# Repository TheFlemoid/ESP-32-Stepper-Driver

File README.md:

### ESP-WROOM-32 Based Stepper Motor Controller

PCB integrating an ESP-WROOM-32 microcontroller with two A4988/DRV8825 stepper motor drivers.

This is a four layer PCB that I originally designed this for an ESP-32 controlled, NEMA17 powered robot.  However it can also be useful for any other application requiring microcontroller control, stepper motors, and any form of SPI or I2C peripheral.

-----

Before connecting and driving the DRV8825, ensure that you set the current limit on both DRV8825/A4988 stepper drivers.

Features include:
 - 'Battery drive'.  Drive the board through a high voltage li-ion or LiPo battery, but enjoy three additional voltage rails:
    - 'Buck', aka the output from the onboard switching buck converter.
    - 5V rail through an onboard 5V LDO.
    - 3V3 rail through an onboard 3V3 LDO.
 - USB-C fast USB programming and UART.
    - USB-C programming for easy cable manipulation, but only fast USB (ie USB 2.0 speed specification) is supported.
    - 'Auto program' (utilizing USB to place the MCU in program mode) is supported.
 - Sleep, step, and direction pin connections for two DRV8825 stepper motor drivers.  Control speed, direction, and sleep on/off (useful for low current operation) for two steppers individually.
    - This was designed with the thought that each controller would be handled via the ESP-32 MCPWM peripheral, but it's entirely feasible to control them through software if desired.
 - Breakout for SPI.
 - Breakout for I2C.
    - Three pins each for both I2C SDA and SCL.
 - Voltage divider / voltmeter for 'battery' voltage.
 - Breakouts for ESP-32 GPIOs 13, 25, 26, and 36.
    - These were unused in the original design, but can be handy for extra outputs (eg another SPI CS pin) or inputs.
 - Pin headers for 1/8, 1/16, and 1/32nd microstepping.
    - Each stepper driver can be independently set for microstepping as required by your application.

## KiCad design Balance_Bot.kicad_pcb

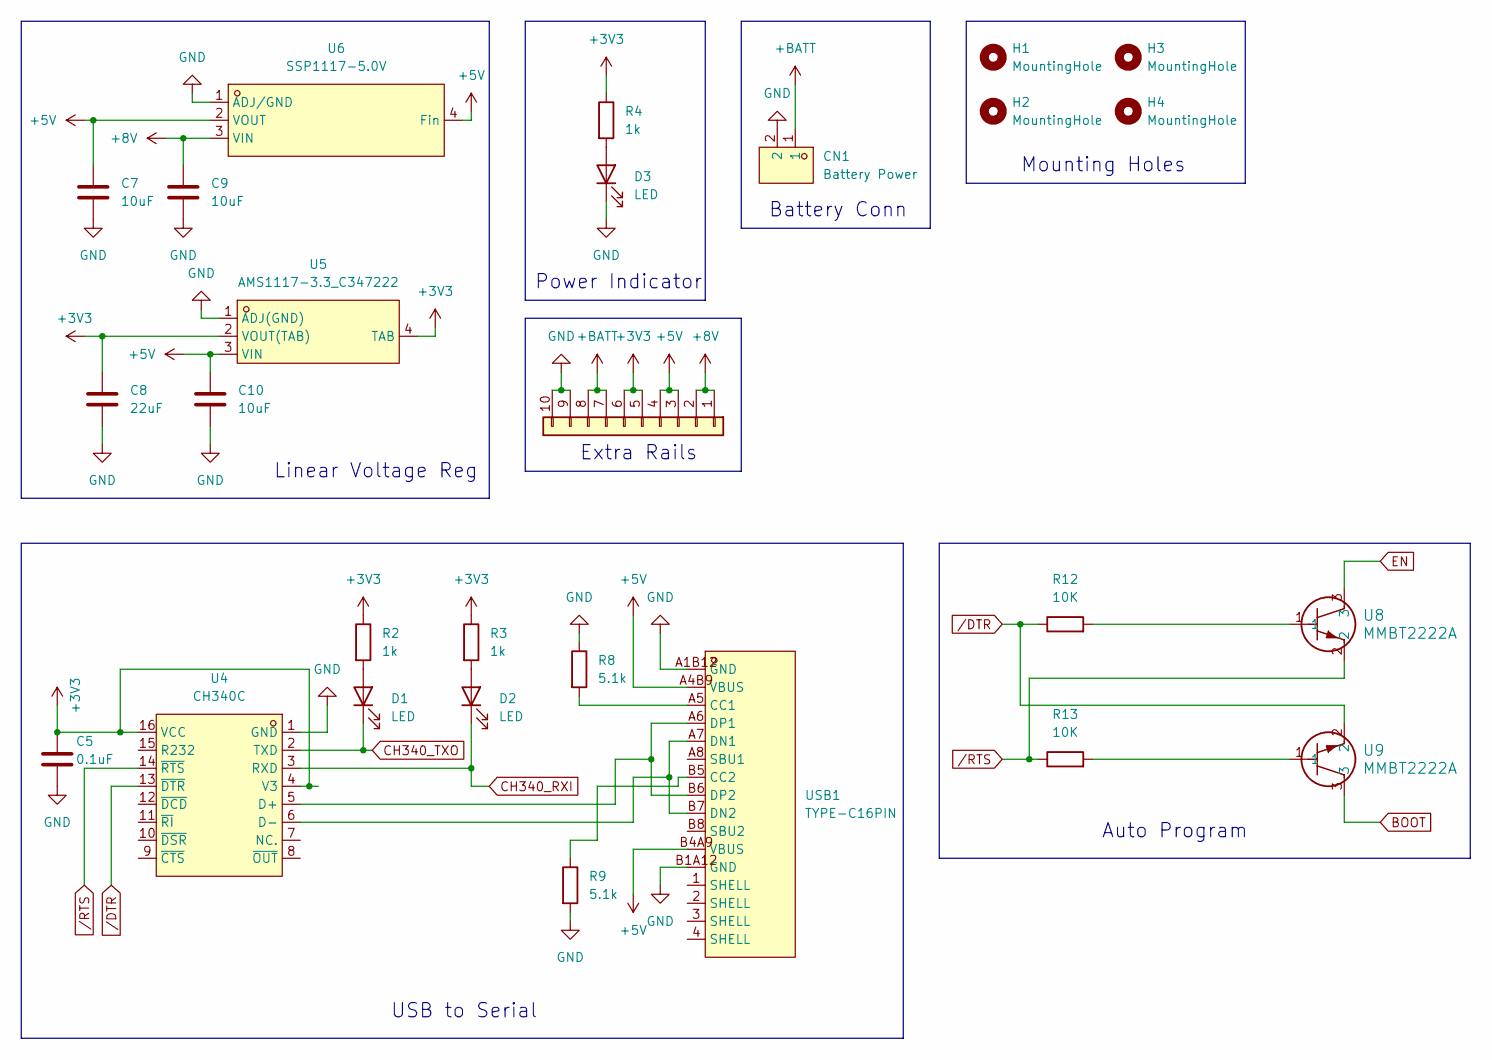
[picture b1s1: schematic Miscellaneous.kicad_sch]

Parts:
C5: 0.1uF; C_0805_2012Metric
C7, C9, C10: 10uF; C_0805_2012Metric
C8: 22uF; C_0805_2012Metric
CN1: Battery Power; CONN-TH_2P-P5.00_MX126-5.0-GN01-02P-CU-S-A; LCSC Part C5188434
D1, D2, D3: LED; LED_0805_2012Metric
H1, H2, H3, H4: MountingHole; MountingHole_2.5mm
J11: Conn_01x10; PinHeader_1x10_P2.54mm_Vertical
R2, R3, R4: 1k; R_0805_2012Metric
R8, R9: 5.1k; R_0805_2012Metric
R12, R13: 10K; R_0805_2012Metric
U4: CH340C; SOP-16_L10.0-W3.9-P1.27-LS6.0-BL; LCSC Part C84681
U5: AMS1117-3.3_C347222; SOT-223-4_L6.5-W3.5-P2.30-LS7.0-BR; LCSC Part C347222
U6: SSP1117-5.0V; SOT-223_L6.5-W3.5-P2.30-LS7.0-BR; LCSC Part C277893
U8, U9: MMBT2222A; SOT23_FAS
USB1: TYPE-C16PIN; USB-C-SMD_TYPE-C16PIN; LCSC Part C393939

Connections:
+3V3: C5.1, C8.1, J11.5, J11.6, R2.1, R3.1, R4.1, U4.4 (V3), U4.16 (VCC), U5.2 (VOUT(TAB)), U5.4 (TAB); also elsewhere on the board
+5V: C7.1, C10.1, J11.3, J11.4, U5.3 (VIN), U6.2 (VOUT), U6.4 (Fin), USB1.A4B9 (VBUS), USB1.B4A9 (VBUS)
+8V: C9.1, J11.1, J11.2, U6.3 (VIN); also elsewhere on the board
+BATT: CN1.1, J11.7, J11.8; also elsewhere on the board
BOOT: U9.3; also elsewhere on the board
CH340_RXI: D2.1 (K), U4.3 (RXD); also elsewhere on the board
CH340_TXO: D1.1 (K), U4.2 (TXD); also elsewhere on the board
EN: U8.3; also elsewhere on the board
GND: C5.2, C7.2, C8.2, C9.2, C10.2, CN1.2, D3.1 (K), J11.9, J11.10, R8.1, R9.2, U4.1 (GND), U5.1 (ADJ(GND)), U6.1 (ADJ/GND), USB1.A1B12 (GND), USB1.B1A12 (GND); also elsewhere on the board
unnamed: D1.2 (A), R2.2
unnamed: D2.2 (A), R3.2
unnamed: D3.2 (A), R4.2
unnamed: R12.2, U8.1
unnamed: R13.2, U9.1
unnamed: U4.5 (D+), USB1.A6 (DP1), USB1.B6 (DP2)
unnamed: U4.6 (D-), USB1.A7 (DN1), USB1.B7 (DN2)
unnamed: R8.2, USB1.A5 (CC1)
unnamed: R9.1, USB1.B5 (CC2)
/DTR: R12.1, U4.13 (~DTR), U9.2
/RTS: R13.1, U4.14 (~RTS), U8.2

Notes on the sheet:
Linear Voltage Reg
Mounting Holes
Extra Rails
USB to Serial
Power Indicator
Auto Program
Battery Conn

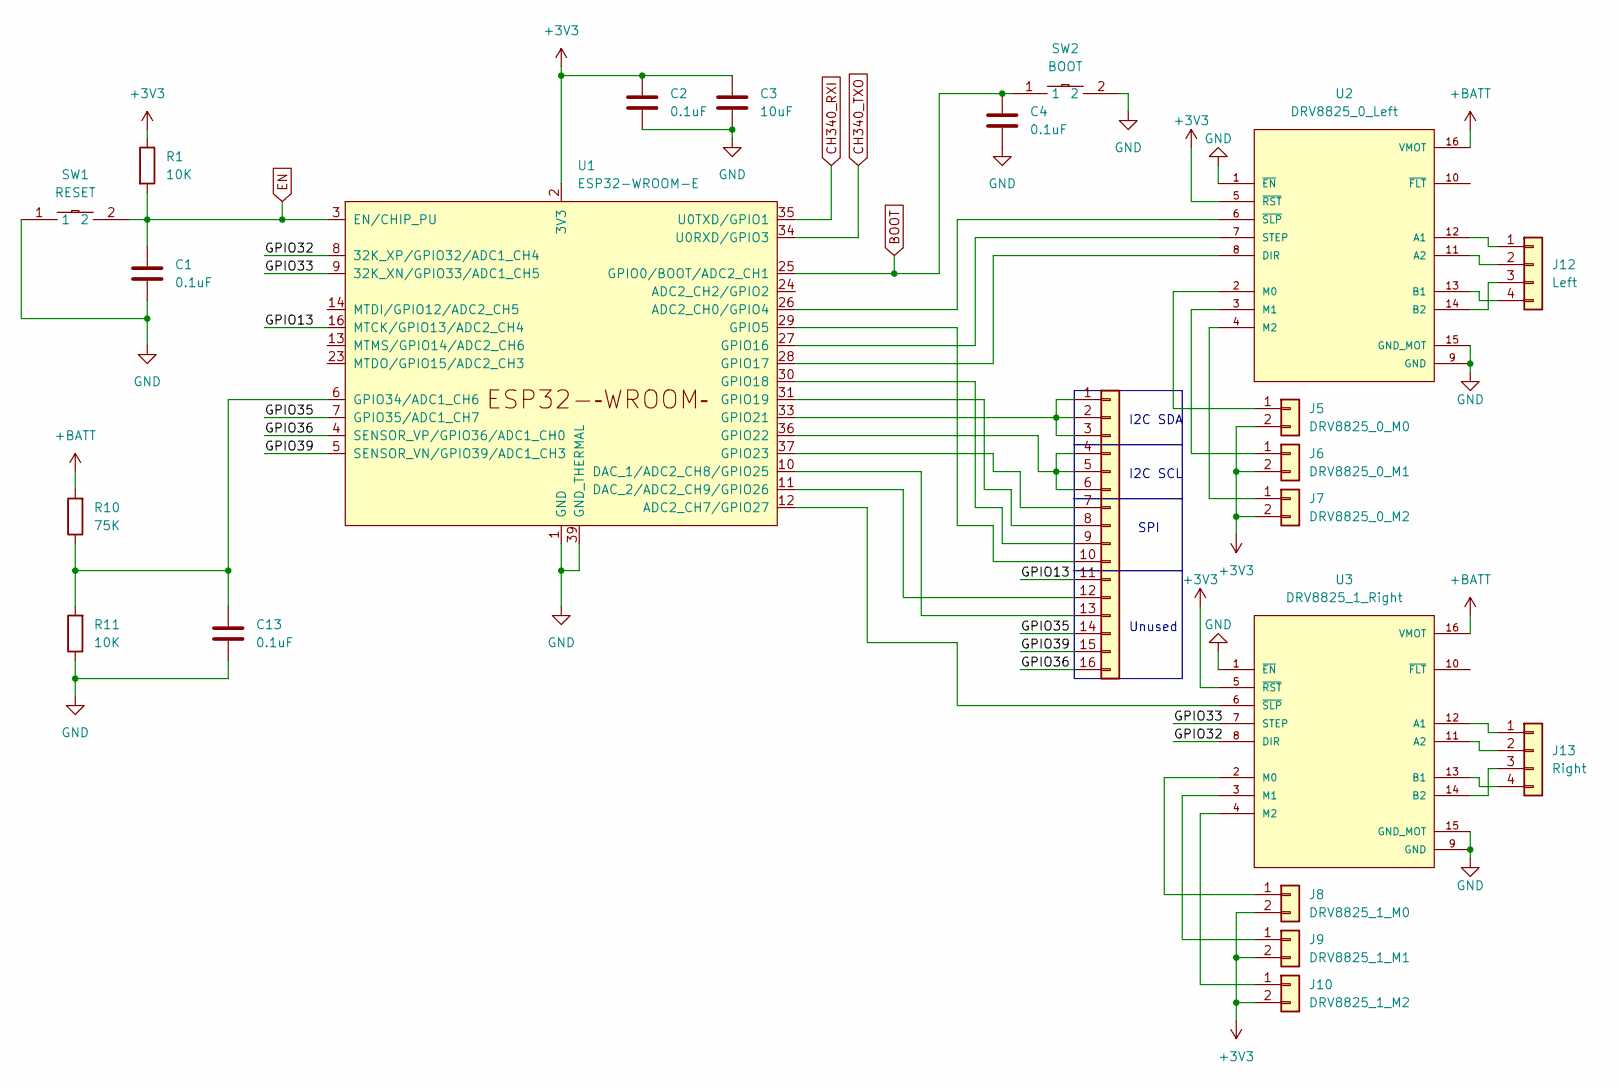
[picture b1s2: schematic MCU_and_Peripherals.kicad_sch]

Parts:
C1, C2, C4, C13: 0.1uF; C_0805_2012Metric
C3: 10uF; C_0805_2012Metric
J5: DRV8825_0_M0; PinHeader_1x02_P2.54mm_Vertical
J6: DRV8825_0_M1; PinHeader_1x02_P2.54mm_Vertical
J7: DRV8825_0_M2; PinHeader_1x02_P2.54mm_Vertical
J8: DRV8825_1_M0; PinHeader_1x02_P2.54mm_Vertical
J9: DRV8825_1_M1; PinHeader_1x02_P2.54mm_Vertical
J10: DRV8825_1_M2; PinHeader_1x02_P2.54mm_Vertical
J12: Left; PinSocket_1x04_P2.54mm_Vertical
J13: Right; PinSocket_1x04_P2.54mm_Vertical
J14: Conn_01x16; PinHeader_1x16_P2.54mm_Vertical
R1, R11: 10K; R_0805_2012Metric
R10: 75K; R_0805_2012Metric
SW1: RESET; SW-SMD_L6.0-W3.3-LS8.0; LCSC Part C318938
SW2: BOOT; SW-SMD_L6.0-W3.3-LS8.0; LCSC Part C318938
U1: ESP32-WROOM-E; ESP32-WROOM-32E
U2: DRV8825_0_Left; IC_DRV8825_STEPPER_MOTOR_DRIVER_CARRIER
U3: DRV8825_1_Right; IC_DRV8825_STEPPER_MOTOR_DRIVER_CARRIER

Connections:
+3V3: C2.1, C3.1, J5.2, J6.2, J7.2, J8.2, J9.2, J10.2, R1.1, U1.2 (3V3), U2.5 (~RST), U3.5 (~RST); also elsewhere on the board
+BATT: R10.2, U2.16 (VMOT), U3.16 (VMOT); also elsewhere on the board
/MCU_and_Peripherals/GPIO13: J14.11, U1.16 (MTCK/GPIO13/ADC2_CH4)
/MCU_and_Peripherals/GPIO32: U1.8 (32K_XP/GPIO32/ADC1_CH4), U3.8 (DIR)
/MCU_and_Peripherals/GPIO33: U1.9 (32K_XN/GPIO33/ADC1_CH5), U3.7 (STEP)
/MCU_and_Peripherals/GPIO35: J14.14, U1.7 (GPIO35/ADC1_CH7)
/MCU_and_Peripherals/GPIO36: J14.16, U1.4 (SENSOR_VP/GPIO36/ADC1_CH0)
/MCU_and_Peripherals/GPIO39: J14.15, U1.5 (SENSOR_VN/GPIO39/ADC1_CH3)
BOOT: C4.1, SW2.1, U1.25 (GPIO0/BOOT/ADC2_CH1); also elsewhere on the board
CH340_RXI: U1.35 (U0TXD/GPIO1); also elsewhere on the board
CH340_TXO: U1.34 (U0RXD/GPIO3); also elsewhere on the board
EN: C1.1, R1.2, SW1.2, U1.3 (EN/CHIP_PU); also elsewhere on the board
GND: C1.2, C2.2, C3.2, C4.2, C13.2, R11.1, SW1.1, SW2.2, U1.1 (GND), U1.15 (GND), U1.38 (GND), U1.39 (GND_THERMAL), U2.1 (~EN), U2.9 (GND), U2.15 (GND_MOT), U3.1 (~EN), U3.9 (GND), U3.15 (GND_MOT); also elsewhere on the board
unnamed: J5.1, U2.2 (M0)
unnamed: J6.1, U2.3 (M1)
unnamed: J7.1, U2.4 (M2)
unnamed: J8.1, U3.2 (M0)
unnamed: J9.1, U3.3 (M1)
unnamed: J10.1, U3.4 (M2)
unnamed: J12.1, U2.12 (A1)
unnamed: J12.2, U2.11 (A2)
unnamed: J12.3, U2.14 (B2)
unnamed: J12.4, U2.13 (B1)
unnamed: J13.1, U3.12 (A1)
unnamed: J13.2, U3.11 (A2)
unnamed: J13.3, U3.14 (B2)
unnamed: J13.4, U3.13 (B1)
unnamed: J14.1, J14.2, J14.3, U1.33 (GPIO21)
unnamed: J14.4, J14.5, J14.6, U1.36 (GPIO22)
unnamed: J14.7, U1.37 (GPIO23)
unnamed: J14.8, U1.31 (GPIO19)
unnamed: J14.9, U1.30 (GPIO18)
unnamed: J14.10, U1.29 (GPIO5)
unnamed: J14.12, U1.11 (DAC_2/ADC2_CH9/GPIO26)
unnamed: J14.13, U1.10 (DAC_1/ADC2_CH8/GPIO25)
unnamed: U1.26 (ADC2_CH0/GPIO4), U2.6 (~SLP)
unnamed: U1.12 (ADC2_CH7/GPIO27), U3.6 (~SLP)
unnamed: U1.27 (GPIO16), U2.7 (STEP)
unnamed: U1.28 (GPIO17), U2.8 (DIR)
unnamed: C13.1, R10.1, R11.2, U1.6 (GPIO34/ADC1_CH6)

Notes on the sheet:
I2C SDA
Unused
SPI
I2C SCL

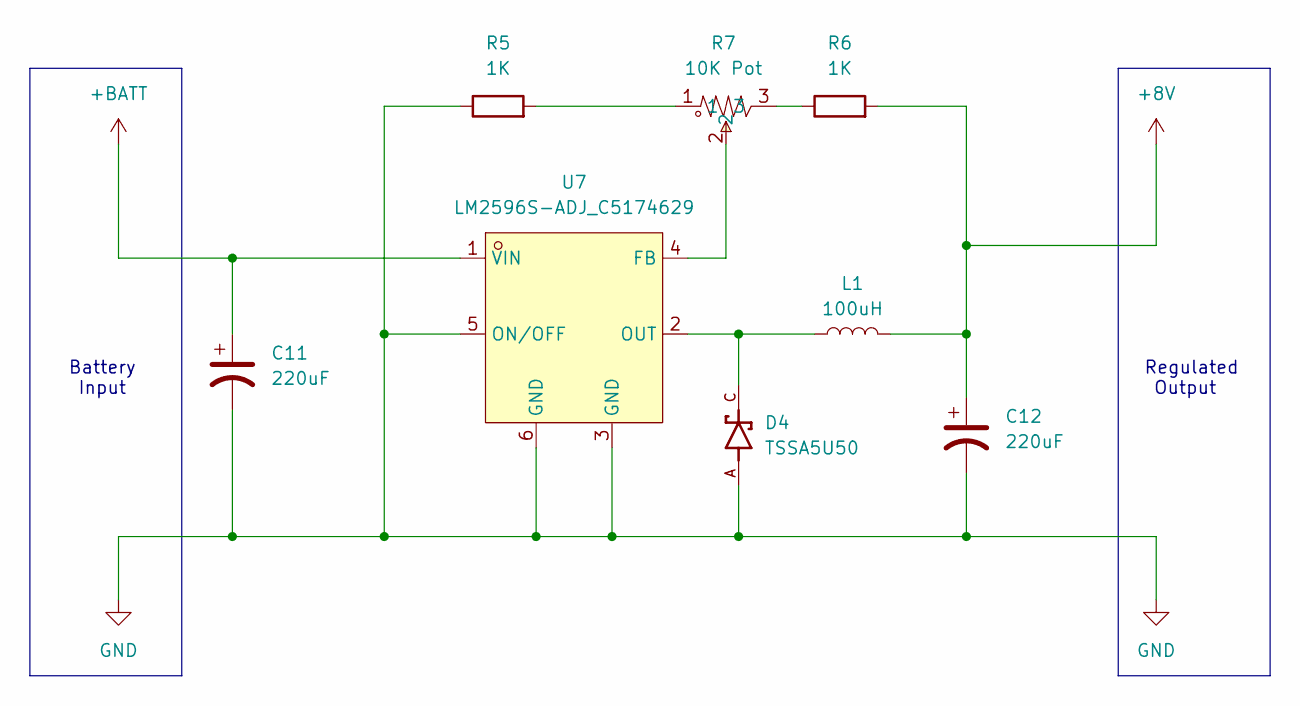
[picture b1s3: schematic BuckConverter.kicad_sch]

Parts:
C11, C12: 220uF; CAP-SMD_BD10.0-L10.3-W10.3-LS11.3-FD
D4: TSSA5U50; DIOM4325X250N; PARTREV O2102
L1: 100uH; IND_BOURNS_SRR1210
R5, R6: 1K; R_0805_2012Metric
R7: 10K Pot; RES-ADJ-TH_3P-L10.0-W10.0-P2.50-L; LCSC Part C118954
U7: LM2596S-ADJ_C5174629; TO-263-5_L10.0-W8.4-P1.70-LS15.3-BR; LCSC Part C5174629

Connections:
+8V: C12.1, L1.2, R6.2; also elsewhere on the board
+BATT: C11.1, U7.1 (VIN); also elsewhere on the board
GND: C11.2, C12.2, D4.A, R5.1, U7.3 (GND), U7.5 (ON/OFF), U7.6 (GND); also elsewhere on the board
unnamed: R5.2, R7.1
unnamed: R6.1, R7.3
unnamed: R7.2, U7.4 (FB)
unnamed: D4.C, L1.1, U7.2 (OUT)

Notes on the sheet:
Regulated Output
Battery Input

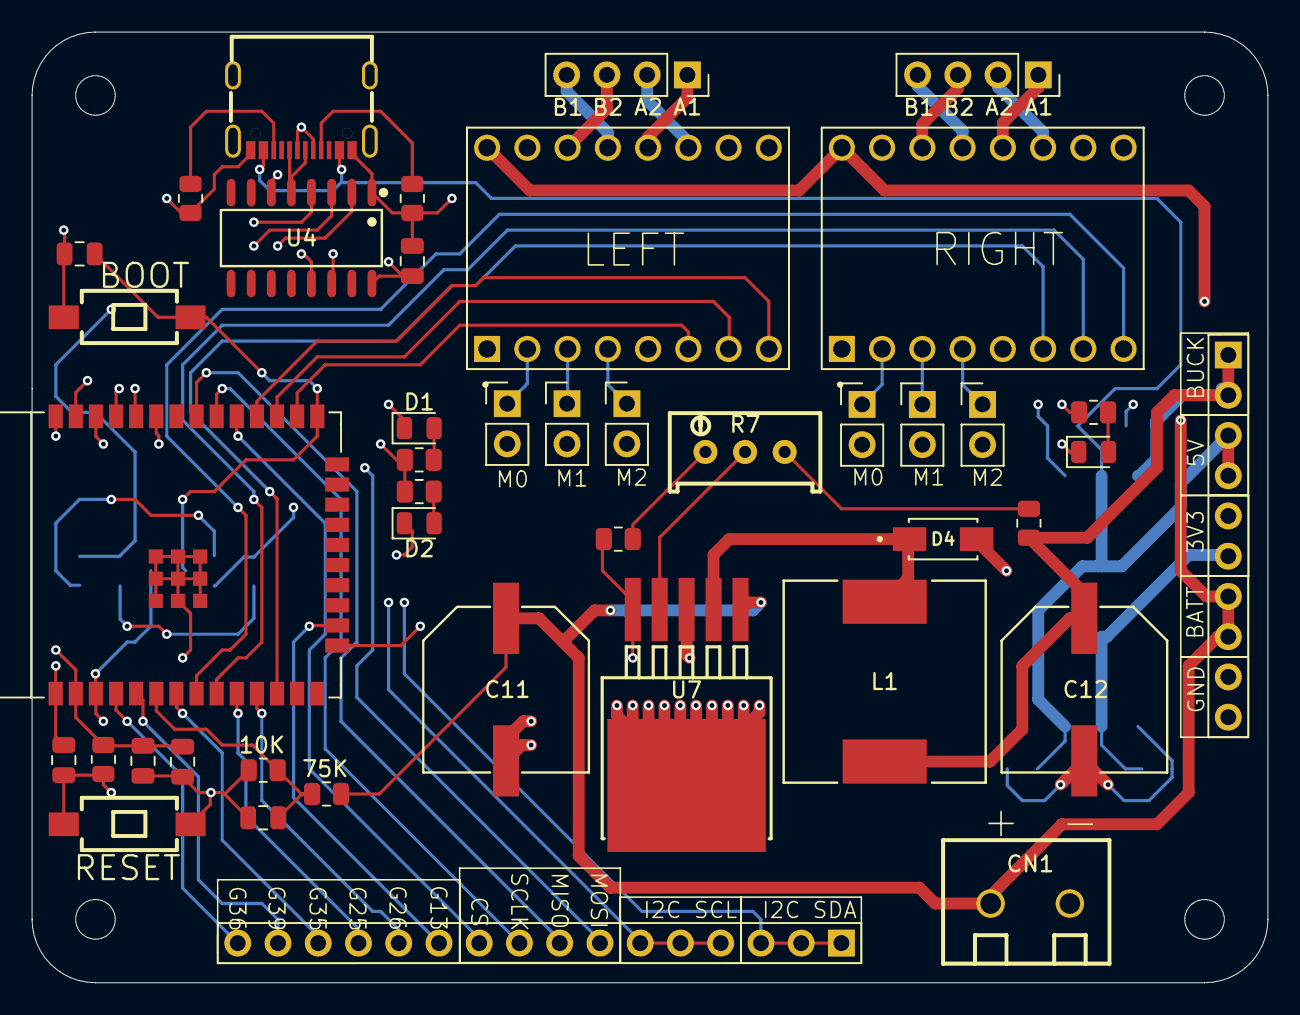
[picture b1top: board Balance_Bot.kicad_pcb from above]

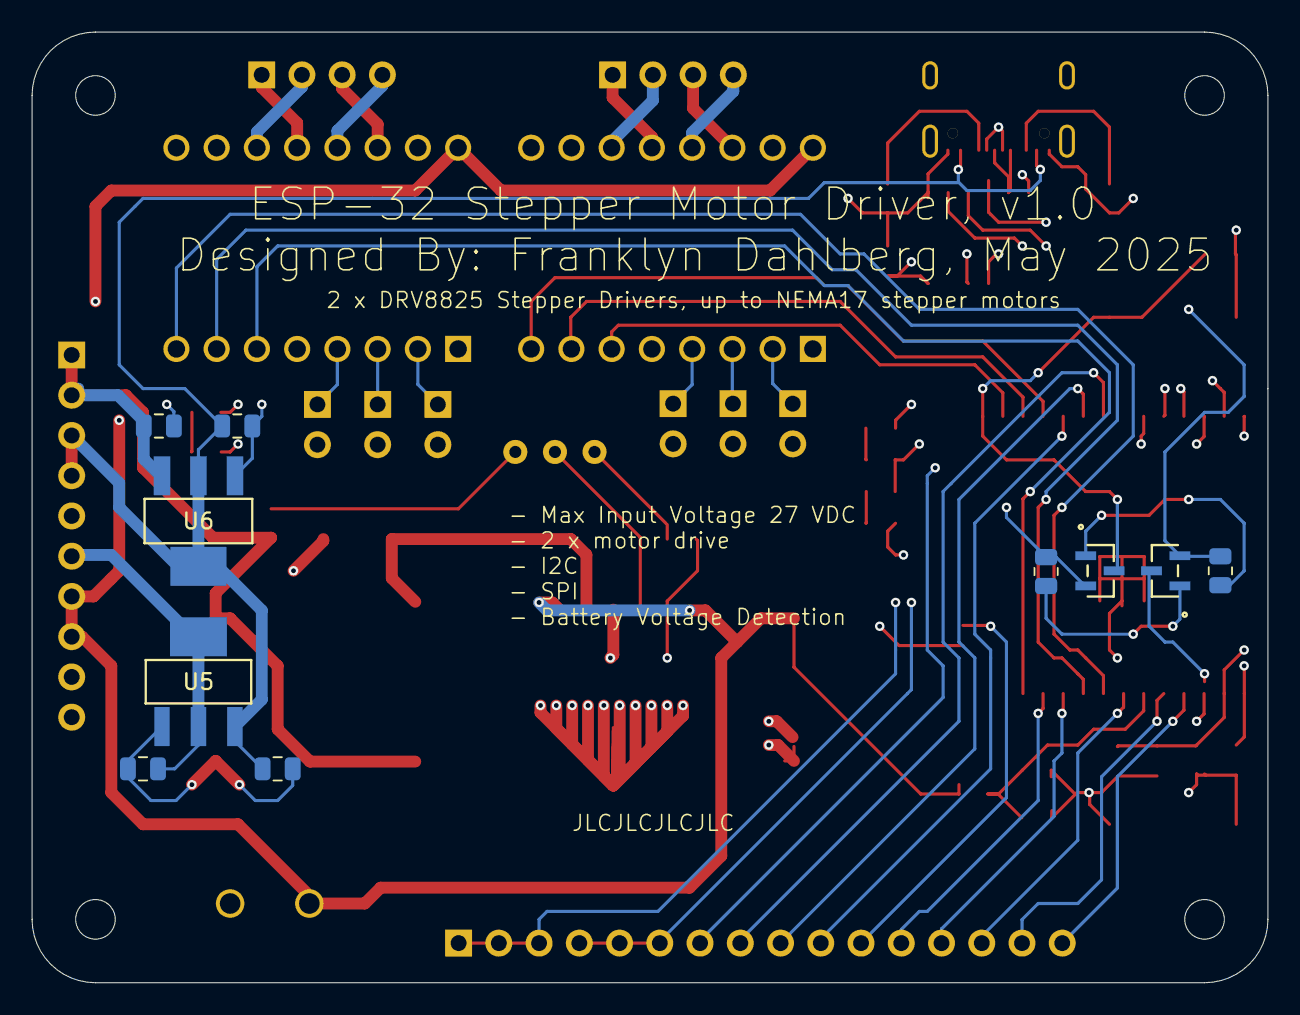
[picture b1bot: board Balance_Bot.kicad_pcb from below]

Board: 4 copper layers, 78.0 x 60.0 mm, 57 parts (10 on the bottom side), 57 nets.

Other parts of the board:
BOOT: BOOT; SW-SMD_L6.0-W3.3-LS8.0
RESET: RESET; SW-SMD_L6.0-W3.3-LS8.0

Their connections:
BOOT: BOOT.1; also elsewhere on the board
EN: RESET.2; also elsewhere on the board
GND: BOOT.2, RESET.1; also elsewhere on the board

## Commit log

2025-05-09 Github Prep (#1)
    Prepping repo to be published onto public GitHub. Made general corrections, wrote a README, and tidied up the repo.
    Reviewed-on: https://git.tdberg.com/TheFlemoid/ESP-32-Stepper-Driver/pulls/1
2025-05-09 Fixing .gitignore
